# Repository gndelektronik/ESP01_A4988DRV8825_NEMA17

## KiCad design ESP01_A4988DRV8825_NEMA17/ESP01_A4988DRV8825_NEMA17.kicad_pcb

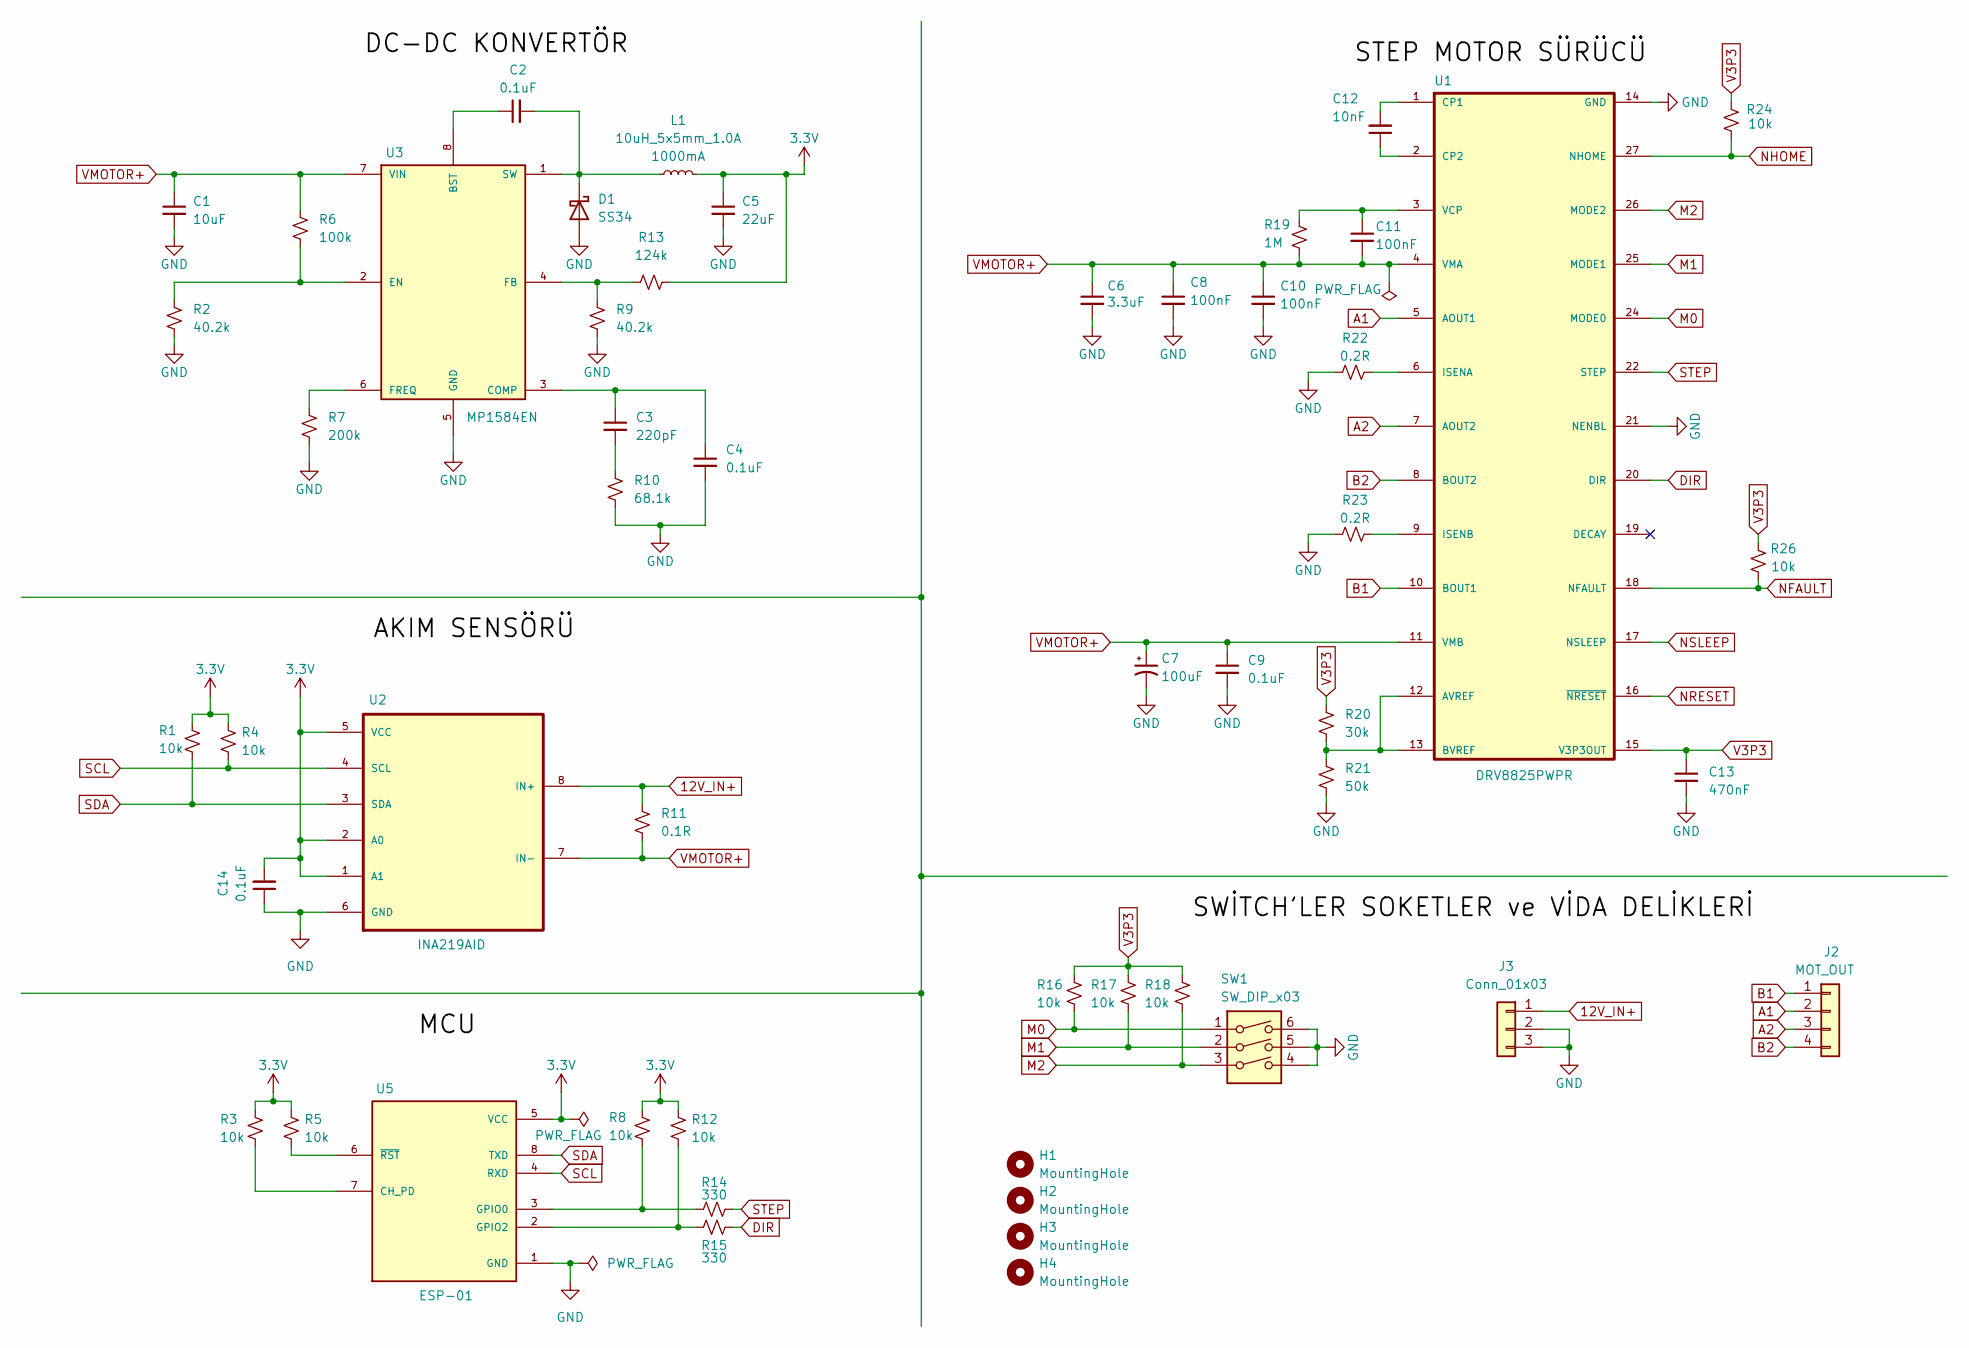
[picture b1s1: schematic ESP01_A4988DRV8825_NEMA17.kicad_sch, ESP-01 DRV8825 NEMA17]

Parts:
C1: 10uF; C_1210_3225Metric; Voltage 50V; Tolerance 20%
C2, C4, C9, C14: 0.1uF; C_0603_1608Metric; Voltage 25V; Tolerance 20%
C3: 220pF; C_0603_1608Metric; Voltage 50V; Tolerance 10%
C5: 22uF; C_0603_1608Metric; Voltage 6.3V; Tolerance 20%
C6: 3.3uF; C_1210_3225Metric; Voltage 100V; Tolerance 10%
C7: 100uF; Panasonic_D; Voltage 25V; Tolerance 20%
C8, C10: 100nF; C_0805_2012Metric; Voltage 100V; Tolerance 10%
C11: 100nF; C_0402_1005Metric; Voltage 100V; Tolerance 10%
C12: 10nF; C_0402_1005Metric; Voltage 50V; Tolerance 10%
C13: 470nF; C_0603_1608Metric; Voltage 50V; Tolerance 10%
D1: SS34; D_SMA
H1, H2, H3, H4: MountingHole; MountingHole_2.5mm
J2: MOT_OUT; JST_PH_B4B-PH-K_1x04_P2.00mm_Vertical
J3: Conn_01x03; Barrel_Jack_PTH
L1: 10uH_5x5mm_1.0A; Inductor_4.7x4.7mm
R1, R3, R4, R5, R8, R12, R16, R17, R18, R26: 10k; R_0603_1608Metric
R2, R9: 40.2k; R_0603_1608Metric
R6: 100k; R_0603_1608Metric
R7: 200k; R_0603_1608Metric
R10: 68.1k; R_0603_1608Metric
R11: 0.1R; R_2512_6332Metric
R13: 124k; R_0603_1608Metric
R14, R15: 330; R_0603_1608Metric
R19: 1M; R_0603_1608Metric
R20: 30k; R_0603_1608Metric
R21: 50k; R_0603_1608Metric
R22, R23: 0.2R; R_2512_6332Metric
R24: 10k; C_0603_1608Metric
SW1: SW_DIP_x03; SW_DIP_SPSTx03_Slide_6.7x9.18mm_W7.62mm_P2.54mm_LowProfile
U1: DRV8825PWPR; IC_TPS61196PWPRQ1
U2: INA219AID; SOIC127P599X175-8N
U3: MP1584EN; SOIC127P600X170-9N
U5: ESP-01; MODULE_ESP-01; PARTREV 1.0

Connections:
3.3V: C5.1, C14.2, L1.2, R1.2, R3.2, R4.2, R5.2, R8.2, R12.2, R13.2, U2.1 (A1), U2.2 (A0), U2.5 (VCC), U5.5 (VCC)
12V_IN+: J3.1, R11.1, U2.8 (IN+)
A1: J2.2, U1.5 (AOUT1)
A2: J2.3, U1.7 (AOUT2)
B1: J2.1, U1.10 (BOUT1)
B2: J2.4, U1.8 (BOUT2)
DIR: R15.2, U1.20 (DIR)
GND: C1.2, C4.2, C5.2, C6.2, C7.2, C8.2, C9.2, C10.2, C13.2, C14.1, D1.2 (A), J3.2, J3.3, R2.1, R7.1, R9.1, R10.1, R21.1, R22.1, R23.1, SW1.4, SW1.5, SW1.6, U1.14 (GND), U1.21 (NENBL), U1.28 (GND), U2.6 (GND), U3.5 (GND), U3.9 (GND), U5.1 (GND)
M0: R16.1, SW1.1, U1.24 (MODE0)
M1: R17.1, SW1.2, U1.25 (MODE1)
M2: R18.1, SW1.3, U1.26 (MODE2)
NFAULT: R26.1, U1.18 (NFAULT)
NHOME: R24.2, U1.27 (NHOME)
NRESET: U1.16 (~NRESET)
NSLEEP: U1.17 (NSLEEP)
unnamed: C3.2, R10.2
unnamed: C2.2, D1.1 (K), L1.1, U3.1 (SW)
unnamed: R20.1, R21.2, U1.12 (AVREF), U1.13 (BVREF)
unnamed: C12.2, U1.1 (CP1)
unnamed: C12.1, U1.2 (CP2)
unnamed: R22.2, U1.6 (ISENA)
unnamed: R23.2, U1.9 (ISENB)
unnamed: C11.1, R19.1, U1.3 (VCP)
unnamed: C2.1, U3.8 (BST)
unnamed: C3.1, C4.1, U3.3 (COMP)
unnamed: R2.2, R6.1, U3.2 (EN)
unnamed: R9.2, R13.1, U3.4 (FB)
unnamed: R7.2, U3.6 (FREQ)
unnamed: R3.1, U5.7 (CH_PD)
unnamed: R8.1, R14.1, U5.3 (GPIO0)
unnamed: R12.1, R15.1, U5.2 (GPIO2)
unnamed: R5.1, U5.6 (~RST)
SCL: R4.1, U2.4 (SCL), U5.4 (RXD)
SDA: R1.1, U2.3 (SDA), U5.8 (TXD)
STEP: R14.2, U1.22 (STEP)
V3P3: C13.1, R16.2, R17.2, R18.2, R20.2, R24.1, R26.2, U1.15 (V3P3OUT)
VMOTOR+: C1.1, C6.1, C7.1, C8.1, C9.1, C10.1, C11.2, R6.2, R11.2, R19.2, U1.4 (VMA), U1.11 (VMB), U2.7 (IN-), U3.7 (VIN)

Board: 2 copper layers, 52 parts (0 on the bottom side), 35 nets, no tracks yet.
